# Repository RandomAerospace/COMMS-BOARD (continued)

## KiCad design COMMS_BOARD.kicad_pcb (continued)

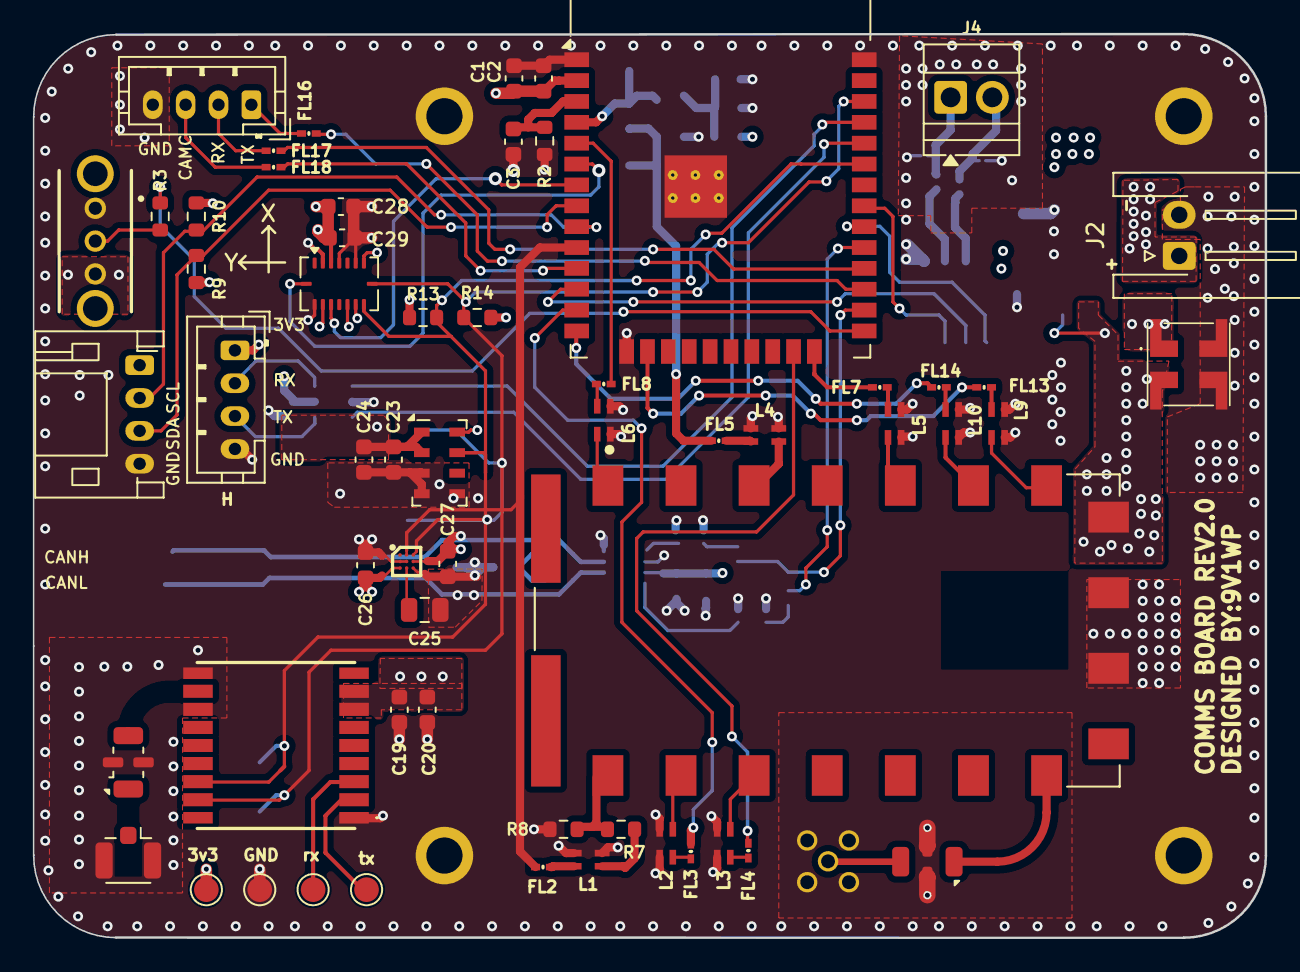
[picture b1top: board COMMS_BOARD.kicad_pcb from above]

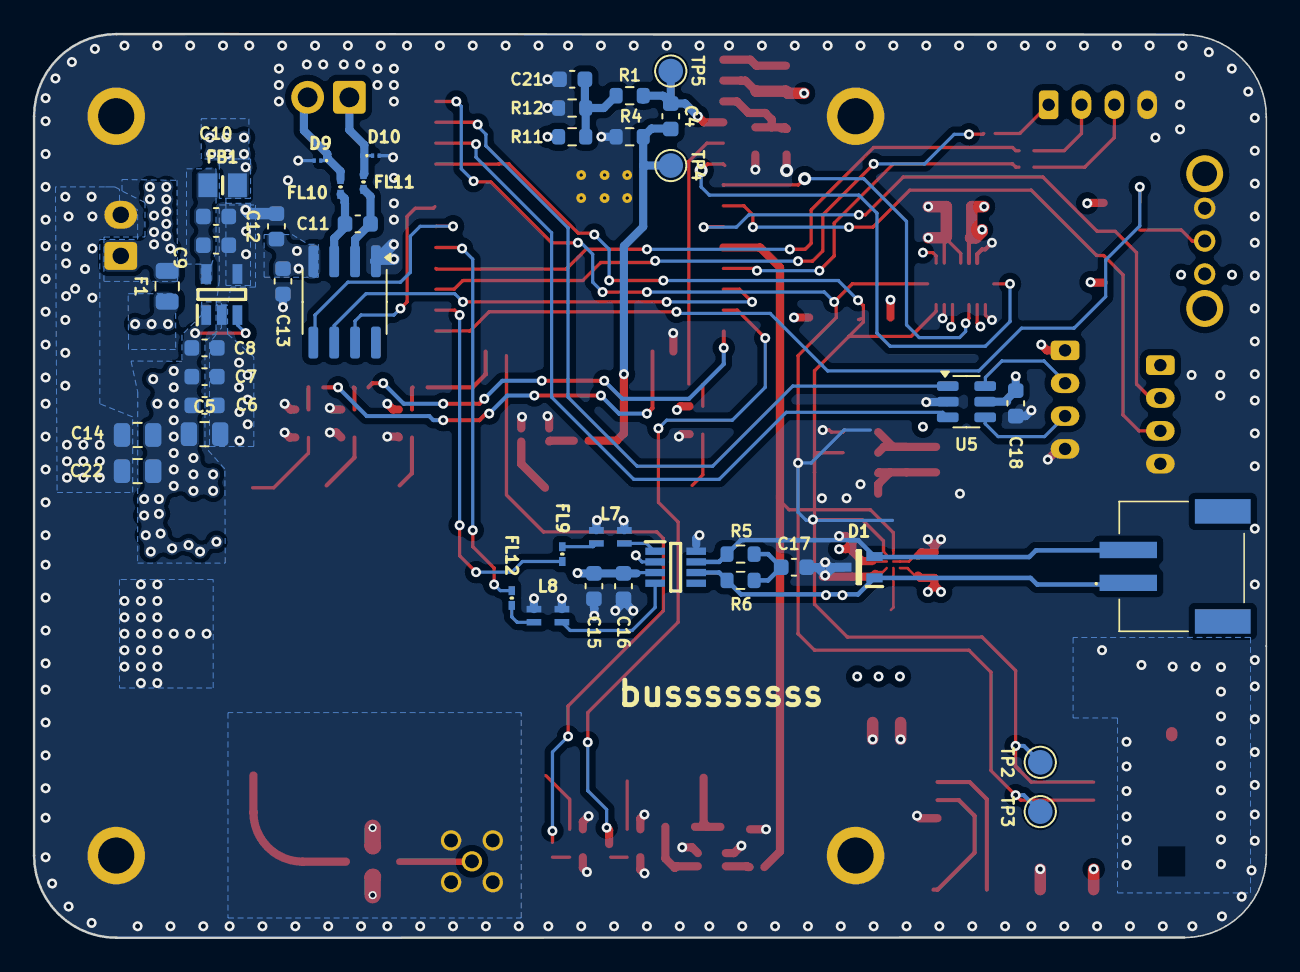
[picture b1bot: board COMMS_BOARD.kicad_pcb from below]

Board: 4 copper layers, 75.0 x 55.0 mm, 107 parts (43 on the bottom side), 73 nets.

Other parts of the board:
FL19: DLW5ATH111TQ2L; DLW5BSN302SQ2L
IC3: MAX-M10S-00B; MAXM10S00B

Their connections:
+3V3: IC3.7 (V_IO), IC3.8 (VCC); also elsewhere on the board
EN_LDO: FL19.2, FL19.6; also elsewhere on the board
GND: FL19.3, FL19.4, FL19.7, FL19.8, IC3.1 (GND_1), IC3.10 (GND_2), IC3.12 (GND_3); also elsewhere on the board
GNSS_UARTRX: IC3.3 (RXD); also elsewhere on the board
GNSS_UARTTX: IC3.2 (TXD); also elsewhere on the board
I2C_SDA: IC3.16 (SDA); also elsewhere on the board
I2C_SDL: IC3.17 (SCL); also elsewhere on the board
unnamed 30: IC3.11 (RF_IN); also elsewhere on the board
VDD: FL19.1, FL19.5; also elsewhere on the board

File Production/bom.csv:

Designator,Footprint,Quantity,Value,LCSC Part #
"C1, C10, C15, C18, C19, C20, C23, C24, C26, C27, C3, C6, C8",0603,13,100nF,
C11,0603,1,10nF,
"C12, C13",0603,2,10uF,
"C14, C22",0805,2,10uF,
"C16, C2, C7, C9",0603,4,1uF,
C17,0603,1,4.7nF,
"C21, C4",0603,2,82n,
"C25, C5",0805,2,4uF,
D1,SOT65P210X110-3N,1,PESD2CANFD24V-UX,
"D10, D3, D8, D9",PMEG3005AESFYL,4,PESD3V3Z1BCSFYL,
D6,PMEG3005AESFYL,1,PESD5V0H1BSFYL,
F1,0805,1,2A @5VDC,
FB1,BEADC2012X105N,1,BLM21PG221SN1D,
"FL10, FL11, FL12, FL13, FL14, FL16, FL17, FL18, FL2, FL3, FL4, FL5, FL7, FL8, FL9",BEADC0603X33N,15,MAF0603FAL330BT000,
FL6,DLW5BSN302SQ2L,1,DLW5ATN112MQ2L,
IC1,SOT65P280X110-8N,1,TCAN1044VDDFR,
IC2,BGA9C40P3X3_128X128X54,1,BMM350,
J1,MMCX_Molex_73415-1471_Vertical,1,Conn_Coaxial_Small,
"J2, J5",JST_XH_B2B-XH-A_1x02_P2.50mm_Vertical,2,Conn_01x02,
"J3, J8",JST_PH_B4B-PH-K_1x04_P2.00mm_Vertical,2,Conn_01x04,
J4,TerminalBlock_Xinya_XY308-2.54-2P_1x02_P2.54mm_Horizontal,1,Screw_Terminal_01x02,
J6,U.FL_Hirose_U.FL-R-SMT-1_Vertical,1,Conn_Coaxial_Small,
J7,JST_PH_B6B-PH-K_1x06_P2.00mm_Vertical,1,Conn_01x06,
"L1, L10, L2, L3, L4, L5, L6, L7, L8, L9",WE-CNSW_08058,10,744231061,
PS1,SOT95P280X145-5N,1,TLV75733PDBVR,
R1,0603,1,100k,
"R10, R13, R14, R9",0603,4,2K4,
R11,0603,1,430,
R12,0603,1,1K6,
"R2, R4",0603,2,10K,
R3,0603,1,1K,
"R5, R6",0603,2,60,
R7,0603,1,2.2K,
R8,0603,1,5.8K,
S2,OS102011MA1QN1,1,OS102011MA1QN1,
"TP1, TP10, TP2, TP3, TP4, TP5, TP8, TP9",TestPoint_Pad_D1.5mm,8,TestPoint,
U1,SOIC-8_3.9x4.9mm_P1.27mm,1,MAX31855KASA,
U3,ESP32-WROOM-32D,1,ESP32-WROOM-32E,
U4,ublox_MAX,1,MAX-M10S,
U5,SOT-23-6,1,USBLC6-2SC6,
U6,LGA-8_3x5mm_P1.25mm,1,MS5611-01BA,

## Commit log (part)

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2026-03-12 FIRST
